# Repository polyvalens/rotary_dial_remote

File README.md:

# Rotary Dial Remote

Introduction

In this project the WIZnet W5100S-EVB-Pico board is used to turn an old analog rotary-dial phone into a remote control and alarm for a home automation system.

[photo]

Even when lights and appliances are controlled by a home automation controller (HAC), it is often desirable to have an override option to switch on or off a lamp, a ventilator or some other device. The modified rotary-dial phone presented here allows this by dialing the number of the appliance. At the same time it forms a now sought-after decorative object.

Besides a remote control for a home automation system, the modified phone can also be used as a prop in for instance an escape game. I am sure many other applications can be imagined too.

The HAC in question is Home Assistant but any controller supporting MQTT can be used.

Functions

The modified rotary-dial phone has the following functions:
- When the handset is on the phone and a number is dialed, the corresponding appliance is switched on or off, depending on its current state.
- When the handset is lifted, the dial can be used to compose a text message in a way similar to mobile phones from some twenty years ago. Replacing the handset on the phone will send the message.
- The bell of the phone is available to the HAC as an alarm and can e.g. be routed to the doorbell or function as a kitchen timer or (unpleasant) wake-up alarm.
- The loudspeaker of the phone will be connected to an MP3 player to play prerecorded messages or music. This allows for implementing for instance a talking clock as was common in the previous century.

Communication between the phone and the HAC uses MQTT, while mDNS is used to establish a connection between the two.

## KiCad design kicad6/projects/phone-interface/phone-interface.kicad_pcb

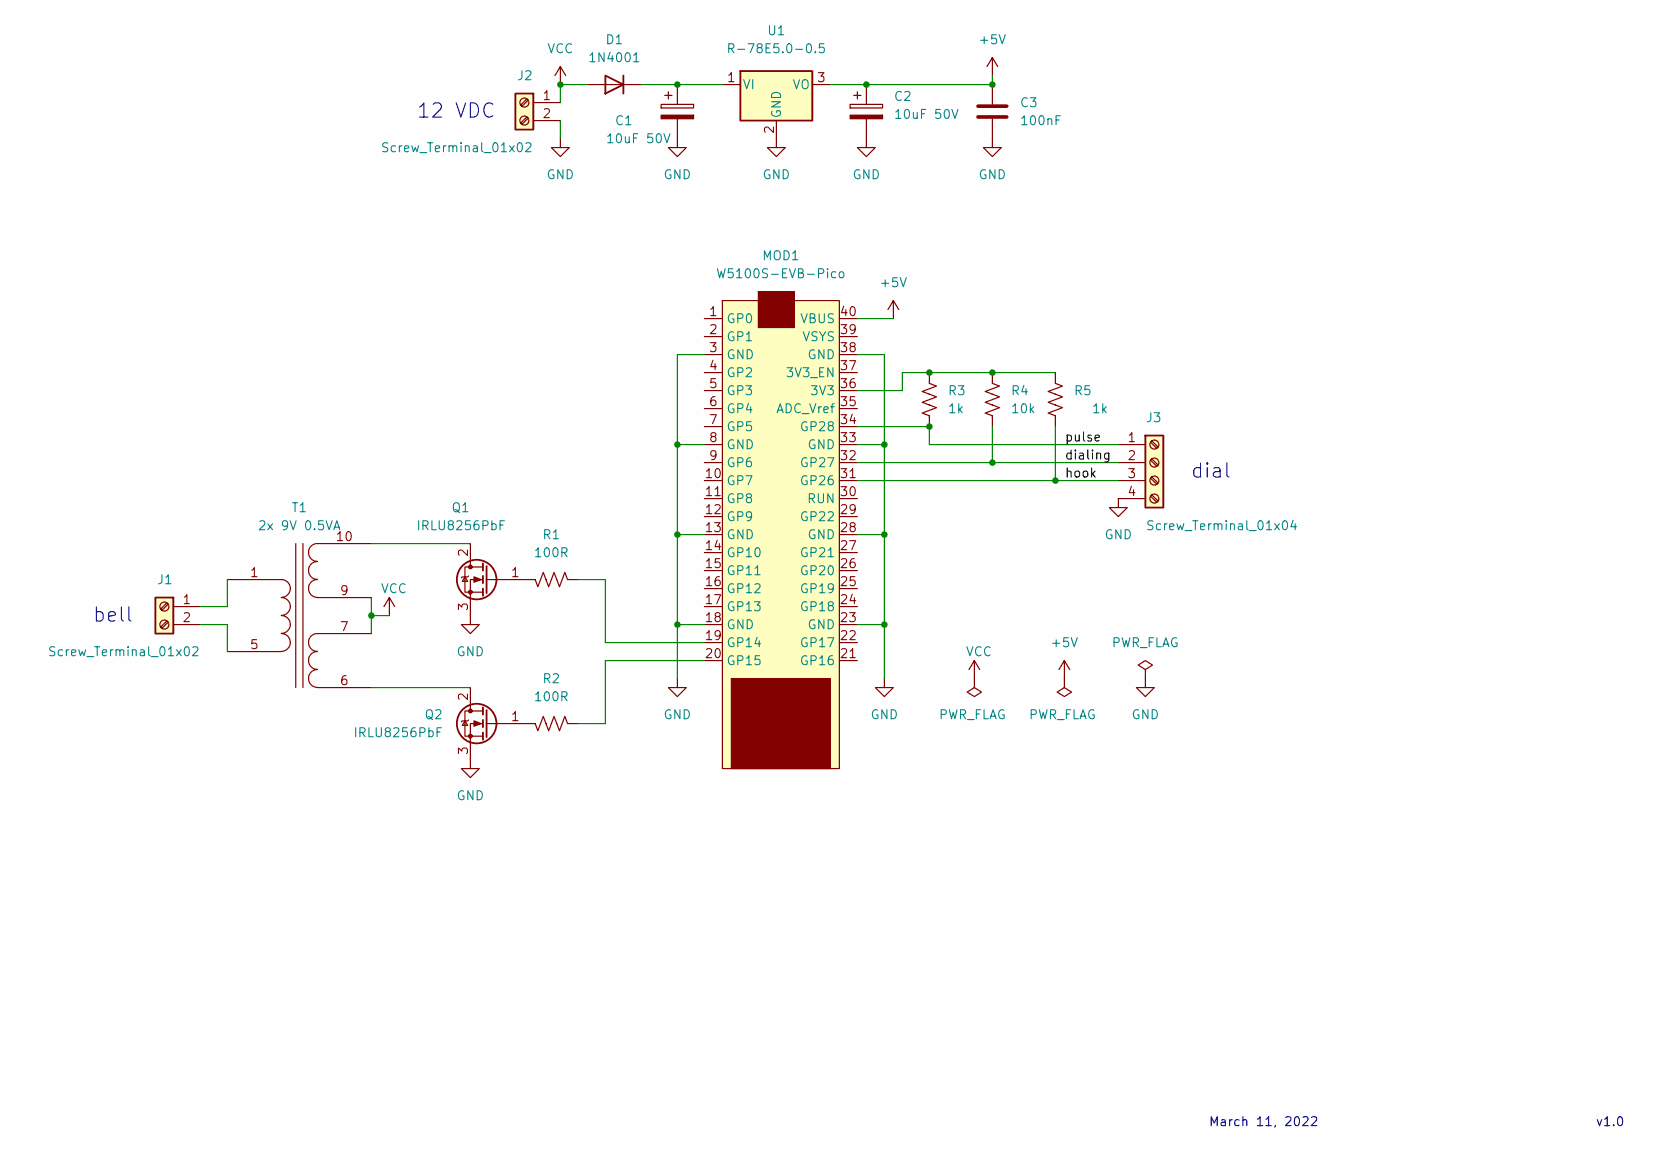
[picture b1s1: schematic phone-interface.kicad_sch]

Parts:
C1, C2: 10uF 50V; CP_Radial_D5.0mm_P2.50mm
C3: 100nF; C_0805_2012Metric_Pad1.18x1.45mm_HandSolder
D1: 1N4001; D_SMA-SMB_Universal_Handsoldering
J1, J2: Screw_Terminal_01x02; TerminalBlock_MetzConnect_Type101_RT01602HBWC_1x02_P5.08mm_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
J3: Screw_Terminal_01x04; TerminalBlock_MetzConnect_Type101_RT01604HBWC_1x04_P5.08mm_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
MOD1: W5100S-EVB-Pico; W5100S-EVB-PICO
Q1, Q2: IRLU8256PbF; TO-220-3_Vertical
R1, R2: 100R; R_0805_2012Metric_Pad1.20x1.40mm_HandSolder
R3, R5: 1k; R_0805_2012Metric_Pad1.20x1.40mm_HandSolder
R4: 10k; R_0805_2012Metric_Pad1.20x1.40mm_HandSolder
T1: 2x 9V 0.5VA; Transformer_myrra_EI30-2VA_2xSec
U1: R-78E5.0-0.5; R-78E

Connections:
+5V: C2.1, C3.1, MOD1.40 (VBUS), U1.3 (VO)
GND: C1.2, C2.2, C3.2, J2.2, J3.4, MOD1.3 (GND), MOD1.8 (GND), MOD1.13 (GND), MOD1.18 (GND), MOD1.23 (GND), MOD1.28 (GND), MOD1.33 (GND), MOD1.38 (GND), Q1.3 (S), Q2.3 (S), U1.2 (GND)
unnamed: C1.1, D1.1 (K), U1.1 (VI)
unnamed: J1.1, T1.1 (AA)
unnamed: J1.2, T1.5 (AB)
unnamed: J3.1, MOD1.34 (GP28), R3.1
unnamed: J3.2, MOD1.32 (GP27), R4.1
unnamed: J3.3, MOD1.31 (GP26), R5.1
unnamed: MOD1.19 (GP14), R1.1
unnamed: MOD1.20 (GP15), R2.1
unnamed: MOD1.36 (3V3), R3.2, R4.2, R5.2
unnamed: Q1.1 (G), R1.2
unnamed: Q1.2 (D), T1.10 (SA)
unnamed: Q2.1 (G), R2.2
unnamed: Q2.2 (D), T1.6 (SD)
VCC: D1.2 (A), J2.1, T1.7 (SC), T1.9 (SB)

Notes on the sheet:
dial
bell
v1.0
March 11, 2022
12 VDC

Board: 2 copper layers, 17 parts (0 on the bottom side), 16 nets, no tracks yet.

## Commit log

2022-06-21 Add files via upload
    Added automatic reconnection.
2022-06-21 Add files via upload
    - Corrected connections of bell HV converter
    - Added LED to pin 6.
